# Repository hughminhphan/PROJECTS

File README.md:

# PROJECTS
 My PCB files for my projects

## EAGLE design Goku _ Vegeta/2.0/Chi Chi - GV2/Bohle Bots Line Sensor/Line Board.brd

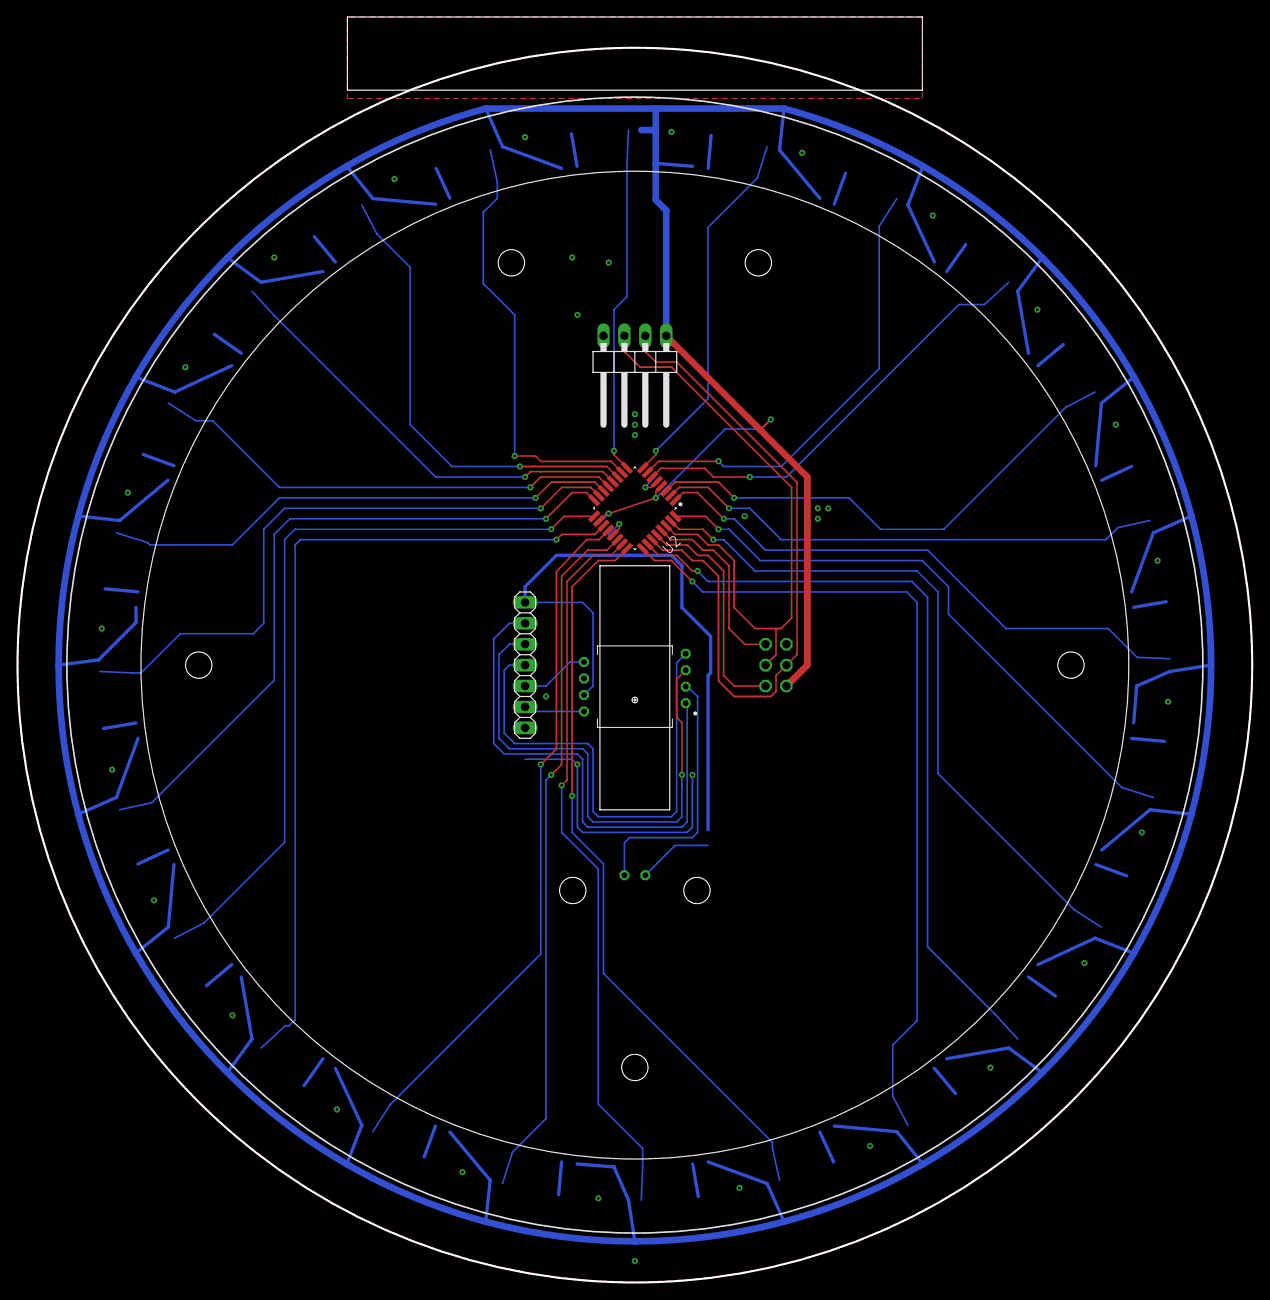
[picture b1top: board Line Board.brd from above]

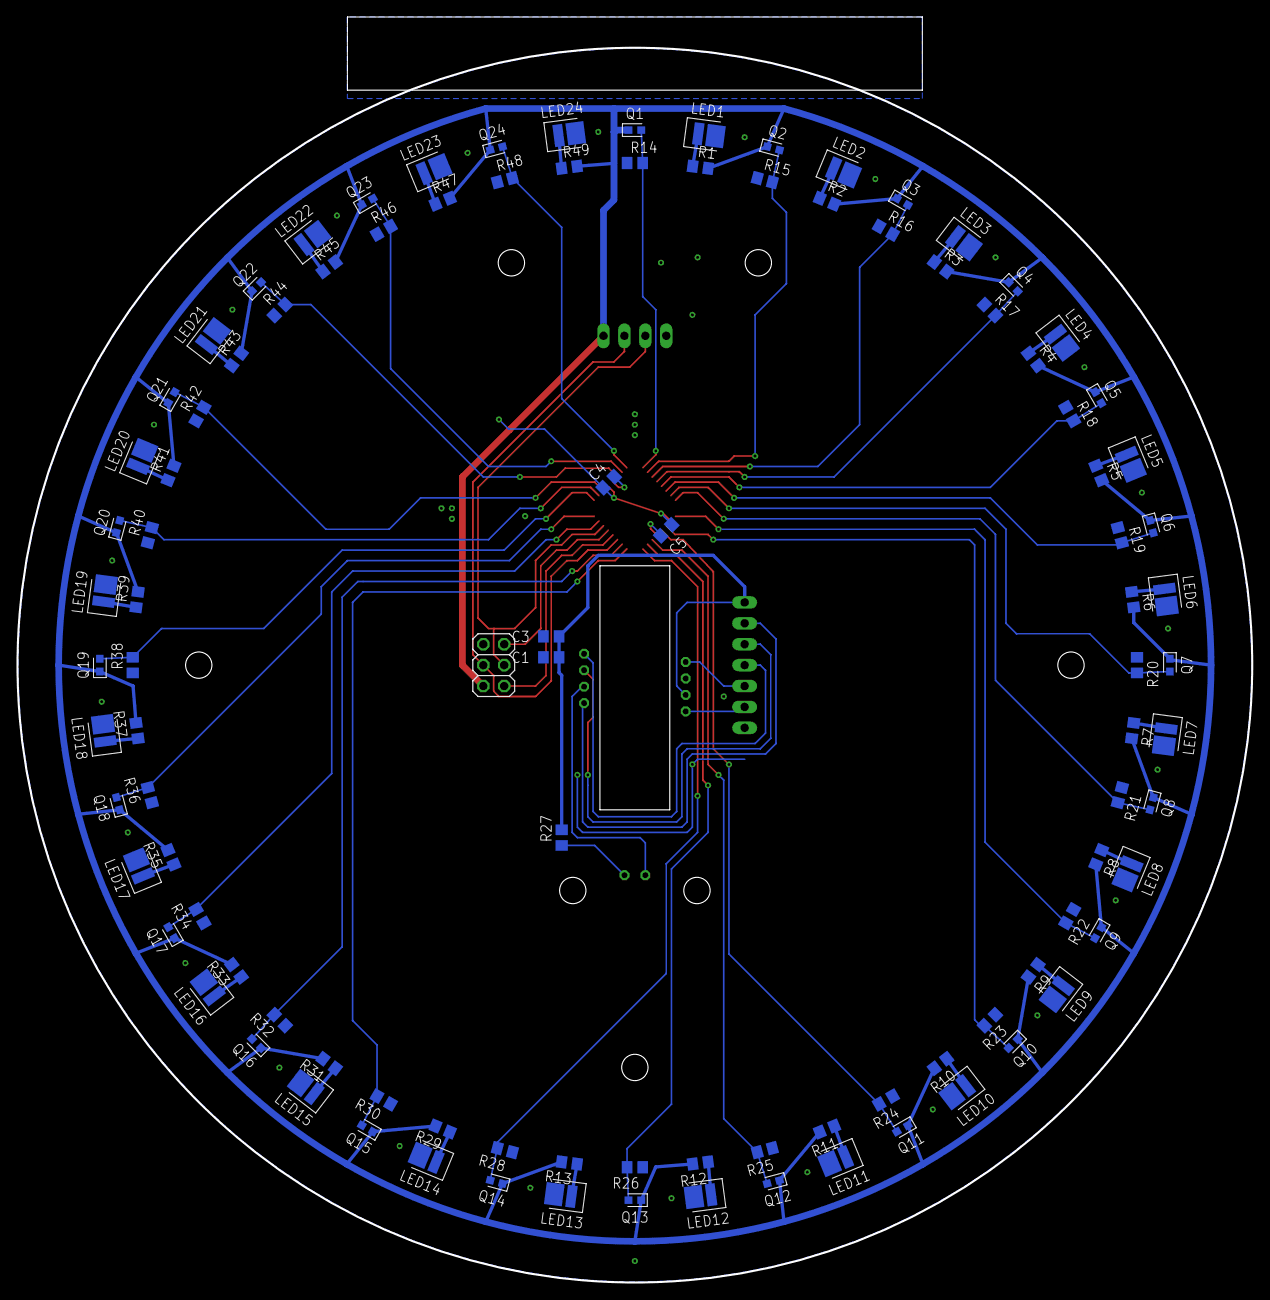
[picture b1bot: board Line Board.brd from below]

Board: 2 copper layers, 150.0 x 153.7 mm, 107 parts (102 on the bottom side), 62 nets.

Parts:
C1, C4, C5: 0.1uF; C0805
C3: 1uF; C0805
JP1: 2X03
JP2: 1X04/90
JP4: 1X07
LED1, LED2, LED3, LED4, LED5, LED6, LED7, LED8, LED9, LED10, LED11, LED12, LED13, LED14, LED15, LED16, LED17, LED18, LED19, LED20, LED21, LED22, LED23, LED24: STW8A12D_LED; LEDC3428X70
Q1, Q2, Q3, Q4, Q5, Q6, Q7, Q8, Q9, Q10, Q11, Q12, Q13, Q14, Q15, Q16, Q17, Q18, Q19, Q20, Q21, Q22, Q23, Q24: ALS-PT19-315C/L177/TR8; LEDC1708X60
R1, R2, R3, R4, R5, R6, R7, R8, R9, R10, R11, R12, R13, R29, R31, R33, R35, R37, R39, R41, R43, R45, R47, R49: 390R; R0805
R14, R15, R16, R17, R18, R19, R20, R21, R22, R23, R24, R25, R26, R28, R30, R32, R34, R36, R38, R40, R42, R44, R46, R48: 10k; R0805
R27: 33R; R0805
U2: ATTINY828; QFP80P900X900X120-32
U3: ADNS3050
U$1: COLORBOARDCUTOUT

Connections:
+3V3: C1.1, C3.1, JP4.1, R27.2, U3.7
+5V: C4.1, C5.1, JP1.2, JP2.1, Q1.C, Q2.C, Q3.C, Q4.C, Q5.C, Q6.C, Q7.C, Q8.C, Q9.C, Q10.C, Q11.C, Q12.C, Q13.C, Q14.C, Q15.C, Q16.C, Q17.C, Q18.C, Q19.C, Q20.C, Q21.C, Q22.C, Q23.C, Q24.C, R1.2, R2.2, R3.2, R4.2, R5.2, R6.2, R7.2, R8.2, R9.2, R10.2, R11.2, R12.2, R13.2, R29.2, R31.2, R33.2, R35.2, R37.2, R39.2, R41.2, R43.2, R45.2, R47.2, R49.2, U2.4, U2.18
COLORSENSOR1: Q1.E, R14.2, U2.9
COLORSENSOR2: Q2.E, R15.2, U2.10
COLORSENSOR3: Q3.E, R16.2, U2.11
COLORSENSOR4: Q4.E, R17.2, U2.12
COLORSENSOR5: Q5.E, R18.2, U2.13
COLORSENSOR6: Q6.E, R19.2, U2.14
COLORSENSOR7: Q7.E, R20.2, U2.15
COLORSENSOR8: Q8.E, R21.2, U2.16
COLORSENSOR9: Q9.E, R22.2, U2.17
COLORSENSOR10: Q10.E, R23.2, U2.19
COLORSENSOR11: Q11.E, R24.2, U2.20
COLORSENSOR12: Q12.E, R25.2, U2.22
COLORSENSOR13: Q13.E, R26.2, U2.23
COLORSENSOR14: Q14.E, R28.2, U2.24
COLORSENSOR15: Q15.E, R30.2, U2.25
COLORSENSOR16: Q16.E, R32.2, U2.26
COLORSENSOR17: Q17.E, R34.2, U2.31
COLORSENSOR18: Q18.E, R36.2, U2.32
COLORSENSOR19: Q19.E, R38.2, U2.1
COLORSENSOR20: Q20.E, R40.2, U2.2
COLORSENSOR21: Q21.E, R42.2, U2.3
COLORSENSOR22: Q22.E, R44.2, U2.6
COLORSENSOR23: Q23.E, R46.2, U2.7
COLORSENSOR24: Q24.E, R48.2, U2.8
GND: C1.2, C3.2, C4.2, C5.2, JP1.6, JP2.4, JP4.7, LED1.2, LED2.2, LED3.2, LED4.2, LED5.2, LED6.2, LED7.2, LED8.2, LED9.2, LED10.2, LED11.2, LED12.2, LED13.2, LED14.2, LED15.2, LED16.2, LED17.2, LED18.2, LED19.2, LED20.2, LED21.2, LED22.2, LED23.2, LED24.2, R14.1, R15.1, R16.1, R17.1, R18.1, R19.1, R20.1, R21.1, R22.1, R23.1, R24.1, R25.1, R26.1, R28.1, R30.1, R32.1, R34.1, R36.1, R38.1, R40.1, R42.1, R44.1, R46.1, R48.1, U2.5, U2.21, U3.6
MISO: JP1.1, U2.28
MOSI/SDA: JP1.4, JP2.2, U2.27
MOUSECS: JP4.4, U3.4
MOUSEMISO: JP4.2, U3.1
MOUSEMOSI: JP4.3, U3.3
MOUSEMOTION: JP4.6, U3.8
MOUSESCK: JP4.5, U3.5
unnamed: LED1.1, R1.1
unnamed: U3.2, U3.K
unnamed: R27.1, U3.A
unnamed: LED2.1, R2.1
unnamed: LED3.1, R3.1
unnamed: LED4.1, R4.1
unnamed: LED5.1, R5.1
unnamed: LED6.1, R6.1
unnamed: LED7.1, R7.1
unnamed: LED8.1, R8.1
unnamed: LED9.1, R9.1
unnamed: LED10.1, R10.1
unnamed: LED11.1, R11.1
unnamed: LED12.1, R12.1
unnamed: LED13.1, R13.1
unnamed: LED14.1, R29.1
unnamed: LED15.1, R31.1
unnamed: LED16.1, R33.1
unnamed: LED17.1, R35.1
unnamed: LED18.1, R37.1
unnamed: LED19.1, R39.1
unnamed: LED20.1, R41.1
unnamed: LED21.1, R43.1
unnamed: LED22.1, R45.1
unnamed: LED23.1, R47.1
unnamed: LED24.1, R49.1
RST: JP1.5, U2.29
SCK/SCL: JP1.3, JP2.3, U2.30

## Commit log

2023-08-14 Intro Epic Commit Test
    testing
2023-08-15 new visor pcb - didnt change anything just checking
2023-08-18 Line 3.0 schematic
2023-08-18 Line 3.0 SCH 1st draft done + started working on SCH for main 3.0
2023-08-18 created sumonyx v2.1
    difference between v2 and v2.1 is that v2.1 is done properly and is made to be cleaner and shipped out
2023-08-19 added notes to sumonyx pcbs
2023-08-22 sumonyx code
    need to get
2023-08-24 sumonyx pcb change to visor ic
2023-08-24 save docs
2023-09-01 Started 3.1 PCBs
2023-09-02 abt halfway done with line 3.0
2023-09-03 Line 3.0 save
2023-09-03 CLEAN UP 3.0 LINE SCH
2023-09-03 line 3.0 - good for the night
2023-09-04 LINE 3.0 - teensy - M driver routing + added teensy programming. + on off switch breakout
2023-09-05 LINE PCB 3.0 BASICALLY DONE!! NOW JUST GOTTA ADD SILKSCREEN!
2023-09-05 LINE 3.0 Update
    -Updated to have caps on power rails
    -imrpoves tolerance of 100uf capacitor
    -main power cable went from xt60 to xt30
    - remove outer wheel guard
2023-09-09 move to 3.1
2023-09-14 MAIN 3.1 DONE no silkscreen
2023-09-15 Main and Line 3.1 done w/ silkscreen
2023-09-16 main 3.1 edit actualy done now i think...
2023-09-16 sch for sumonyx 2.1 pcb
2023-09-16 commit b4 sleep
2023-09-17 main 3.1 fixup
2023-09-17 new mfr for pcbs
2023-12-15 kjwefqkwenfqerlgk
2024-09-15 name change for windows compatibility
    totlololoo
2024-09-15 sbrcotnrollerm update from windows laptop
    dcefefefefe
2024-09-15 what is happening
2024-09-15 ready for mfr
2024-09-15 sbr2code
2024-09-15 demo
2024-09-17 updated code
2024-09-19 pcb mfr
2024-09-20 troll
2024-10-08 sbr lol and the like
2025-01-09 testing the sync
2025-01-09 rgrgrg
